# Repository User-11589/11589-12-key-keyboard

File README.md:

12 key keyboard with the intended keys being in order top to bottom left to right;
esc (next row), shift, q, w, e (nr), ctrl, a, s, d (nr), space.
i realized after the fact that the pcb doesnt allow for screw holes so ignore the holes in the stl files
i havent as of yet written the code for the arduino controller but once i do ill upload.

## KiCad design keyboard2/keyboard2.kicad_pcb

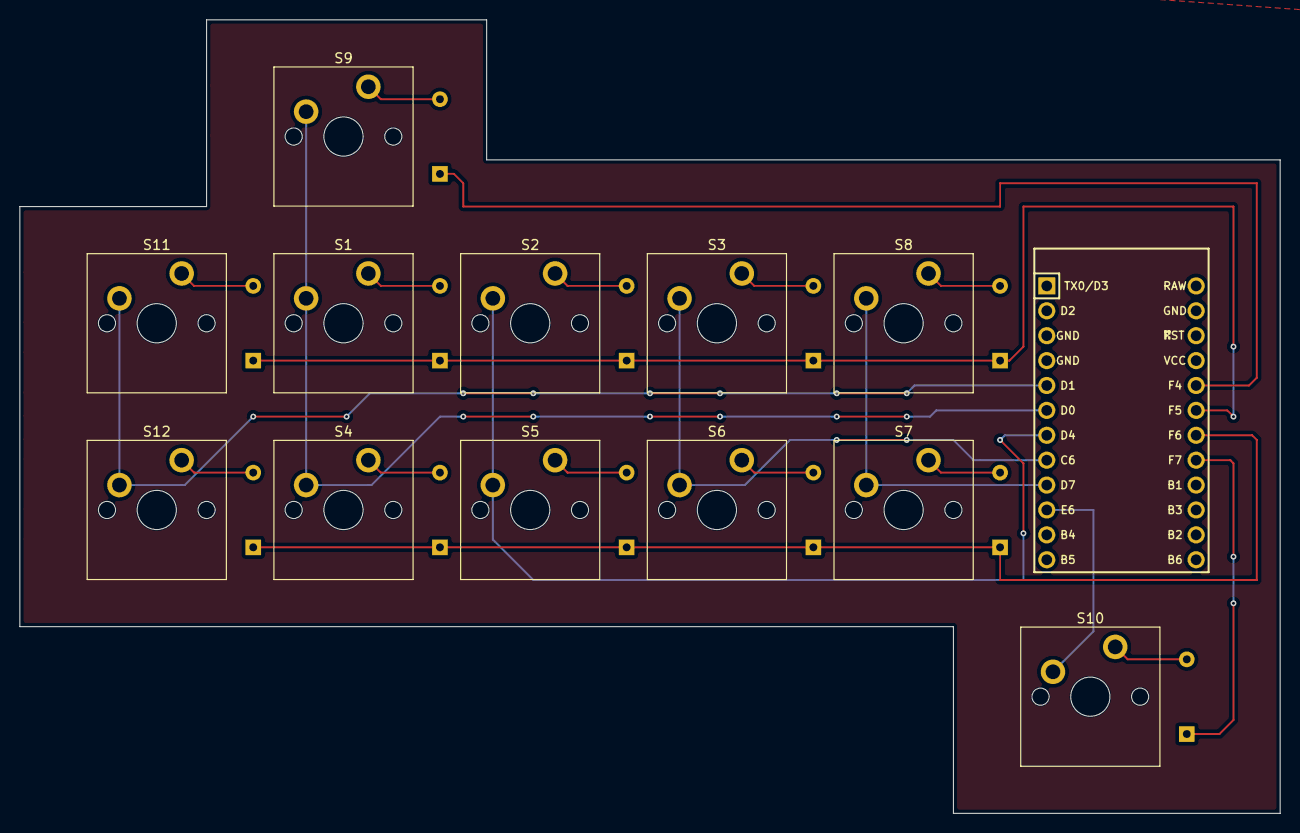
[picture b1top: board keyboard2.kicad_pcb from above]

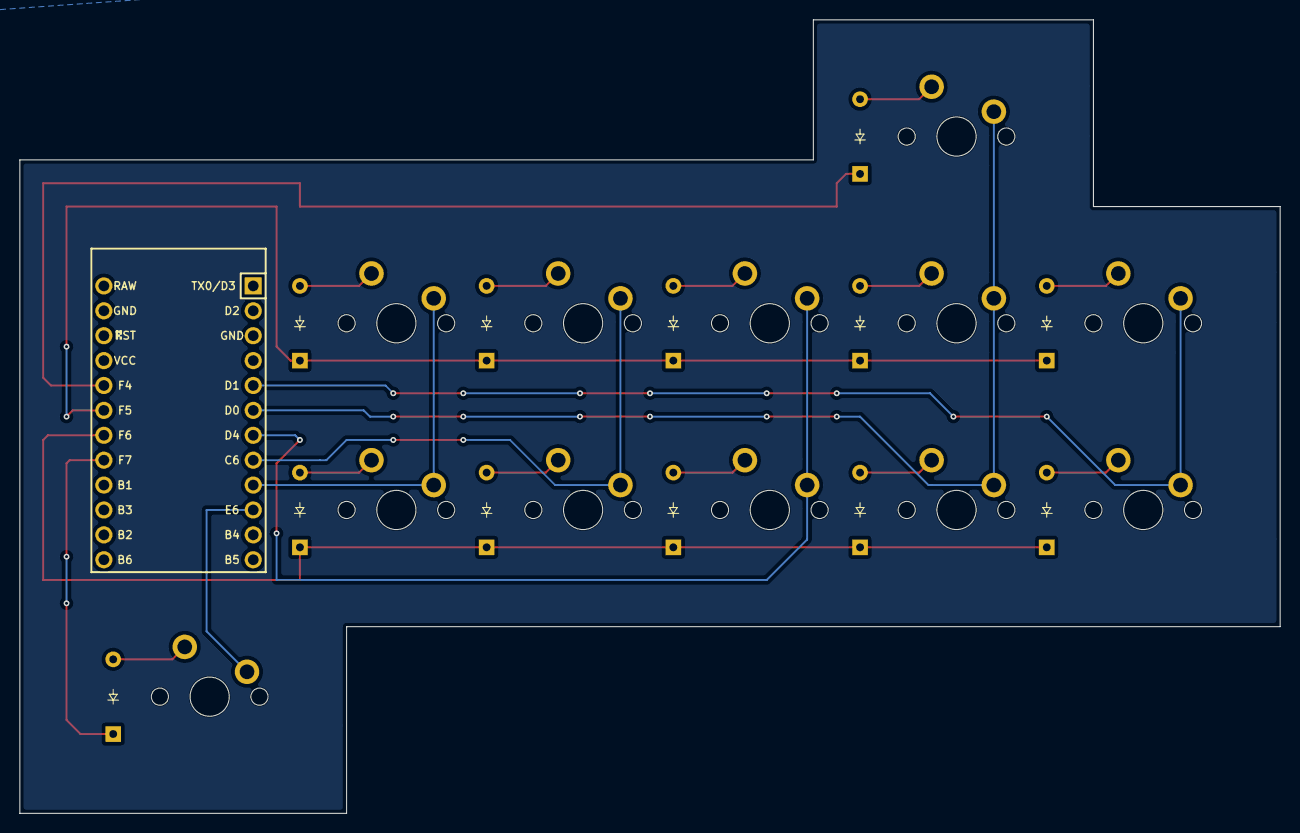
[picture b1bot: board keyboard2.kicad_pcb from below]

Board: 2 copper layers, 128.6 x 81.0 mm, 25 parts (12 on the bottom side), 22 nets.

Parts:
D1, D2, D3, D4, D5, D6, D7, D8, D9, D10, D11, D12: Diode_DO-35
S1, S2, S3, S4, S5, S6, S7, S8, S9, S10, S11, S12: MX_PCB_1.00u
U1: Arduino_Pro_Micro

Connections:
unnamed: D1.2 (A), S1.2
unnamed: D2.2 (A), S2.2
unnamed: D3.2 (A), S3.2
unnamed: D4.2 (A), S4.2
unnamed: D5.2 (A), S5.2
unnamed: D6.2 (A), S6.2
unnamed: D7.2 (A), S7.2
unnamed: D8.2 (A), S8.2
unnamed: D9.2 (A), S9.2
unnamed: D10.2 (A), S10.2
unnamed: D11.2 (A), S11.2
unnamed: D12.2 (A), S12.2
c0: S11.1, S12.1, U1.5 (2/PD1)
c1: S1.1, S4.1, S9.1, U1.6 (3/PD0)
c2: S2.1, S5.1, U1.7 (4/PD4)
c3: S3.1, S6.1, U1.8 (5/PC6)
c4: S7.1, S8.1, U1.9 (6/PD7)
c5: S10.1, U1.10 (7/PE6)
r0: D9.1 (K), U1.20 (A3/PF4)
r1: D1.1 (K), D2.1 (K), D3.1 (K), D8.1 (K), D11.1 (K), U1.19 (A2/PF5)
r2: D4.1 (K), D5.1 (K), D6.1 (K), D7.1 (K), D12.1 (K), U1.18 (A1/PF6)
r3: D10.1 (K), U1.17 (A0/PF7)

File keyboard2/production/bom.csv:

Designator,Footprint,Quantity,Value,LCSC Part #
"D1, D10, D11, D12, D2, D3, D4, D5, D6, D7, D8, D9",Diode_DO-35,12,~,
"S1, S10, S11, S12, S2, S3, S4, S5, S6, S7, S8, S9",MX_PCB_1.00u,12,~,
U1,Arduino_Pro_Micro,1,Arduino_Pro_Micro,
